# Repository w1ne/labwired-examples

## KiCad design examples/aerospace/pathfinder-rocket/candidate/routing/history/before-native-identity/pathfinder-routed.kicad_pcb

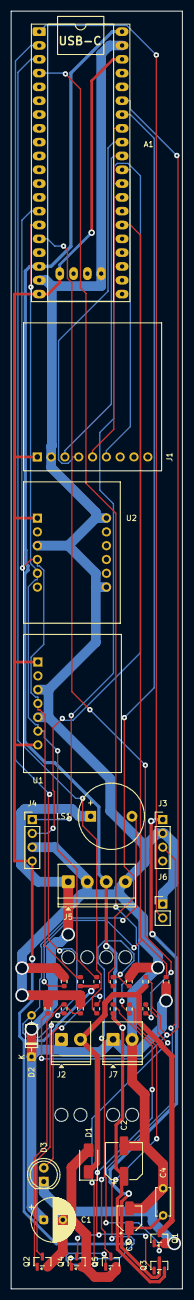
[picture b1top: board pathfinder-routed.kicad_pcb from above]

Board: 2 copper layers, 31.5 x 235.0 mm, 37 parts (0 on the bottom side), 30 nets.

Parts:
A1: MiniSTM32F411; WeAct-BlackPill-v31-body-envelope
C1: 470uF; CP_Radial_D8.0mm_P3.50mm
C2: 22uF; CP_Elec_6.3x5.4
C3: 10uF; CP_Elec_4x5.4
C4: 100nF; C_Disc_D5.0mm_W2.5mm_P5.00mm
D1: SMAJ5.0A; D_SMA
D2: 1N4148; D_DO-35_SOD27_P7.62mm_Horizontal
D3: green; LED_D5.0mm
J1: 4682; Adafruit_MicroSD_4682_CardEnvelope
J2, J7: 1984617; TerminalBlock_Phoenix_PT-1,5-2-3.5-H_1x02_P3.50mm_Horizontal
J3, J4: pin-header; PinHeader_1x04_P2.54mm_Vertical
J5: 1984633; TerminalBlock_Phoenix_PT-1,5-4-3.5-H_1x04_P3.50mm_Horizontal
J6: pin-header; PinHeader_1x02_P2.54mm_Vertical
LS1: 1536; Buzzer_12x9.5RM7.6
Q1: AO3400A; SOT-23
Q2: 2N7000; SOT-23
Q3: AO3401A; SOT-23
Q4, Q5: 2N3904; SOT-23
R1, R2, R8: 100000; R_0603_1608Metric
R3, R4: 4700; R_0603_1608Metric
R5, R9: 100; R_0603_1608Metric
R6, R10, R12: 10000; R_0603_1608Metric
R7: 47000; R_0603_1608Metric
R11: 330; R_0603_1608Metric
R13, R14: 1000; R_0603_1608Metric
U1: 2652; Adafruit_BME280_QT
U2: 3886; Adafruit_MPU6050

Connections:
+: C1.1, D2.1, J2.1, J5.1, J7.1, LS1.1, R1.1
+3V3: A1.20, A1.38, A1.41, C3.1, C4.1, J1.1, J4.4, R3.1, R4.1, U1.1, U1.7, U2.1
+5V: A1.18, A1.40, C2.1, J5.3, Q3.2, R12.1
GND: A1.19, A1.39, A1.44, C1.2, C2.2, C3.2, C4.2, D1.2, D3.1, J1.2, J3.2, J4.3, J5.2, J5.4, J6.1, J7.2, Q1.2, Q2.2, Q4.2, Q5.2, R2.2, R6.2, R8.2, R10.2, U1.3, U1.5, U2.3, U2.7, U2.12
unnamed: D2.2, LS1.2, Q2.3
unnamed: J3.1, Q3.3
unnamed: J3.3, Q5.3
unnamed: D1.1, J2.2, Q1.3, R7.1
unnamed: D3.2, R11.2
unnamed: Q2.1, R9.2, R10.1
unnamed: Q4.1, R13.2
unnamed: Q3.1, Q4.3, R12.2
unnamed: Q1.1, R5.2, R6.1
unnamed: Q5.1, R14.2
PA0: A1.26, R1.2, R2.1
PA2: A1.28, J4.1
PA3: A1.29, J4.2
PA4: A1.30, J1.6
PA5: A1.31, J1.3
PA6: A1.32, J1.4
PA7: A1.33, J1.5
PB0: A1.34, R5.1
PB1: A1.35, R7.2, R8.1
PB6: A1.14, R3.2, U1.4, U2.4
PB7: A1.15, R4.2, U1.6, U2.5
PB8: A1.16, R14.1
PB12: A1.1, J6.2
PB13: A1.2, R9.1
PB14: A1.3, R11.1
PB15: A1.4, R13.1

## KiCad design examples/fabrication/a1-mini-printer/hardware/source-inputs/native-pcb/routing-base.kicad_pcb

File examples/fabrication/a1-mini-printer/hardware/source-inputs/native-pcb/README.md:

# Routing input

`routing-base.kicad_pcb` is the fixed native output from the KiCad 10 / Freerouting 2.5.0 routing exchange. It is an intermediate input, not the accepted board. The final source applies explicit copper, topology, polarity and package corrections, then passes independent KiCad DRC.

The exact accepted starting board and original project rules are preserved under the verification evidence as `accepted-baseline/`. The original three missing nets were END_X, END_Y and Z_DIR. The routing input has all three closed; the deterministic patch sequence finishes the remaining escapes and applies the authorized electrical corrections.

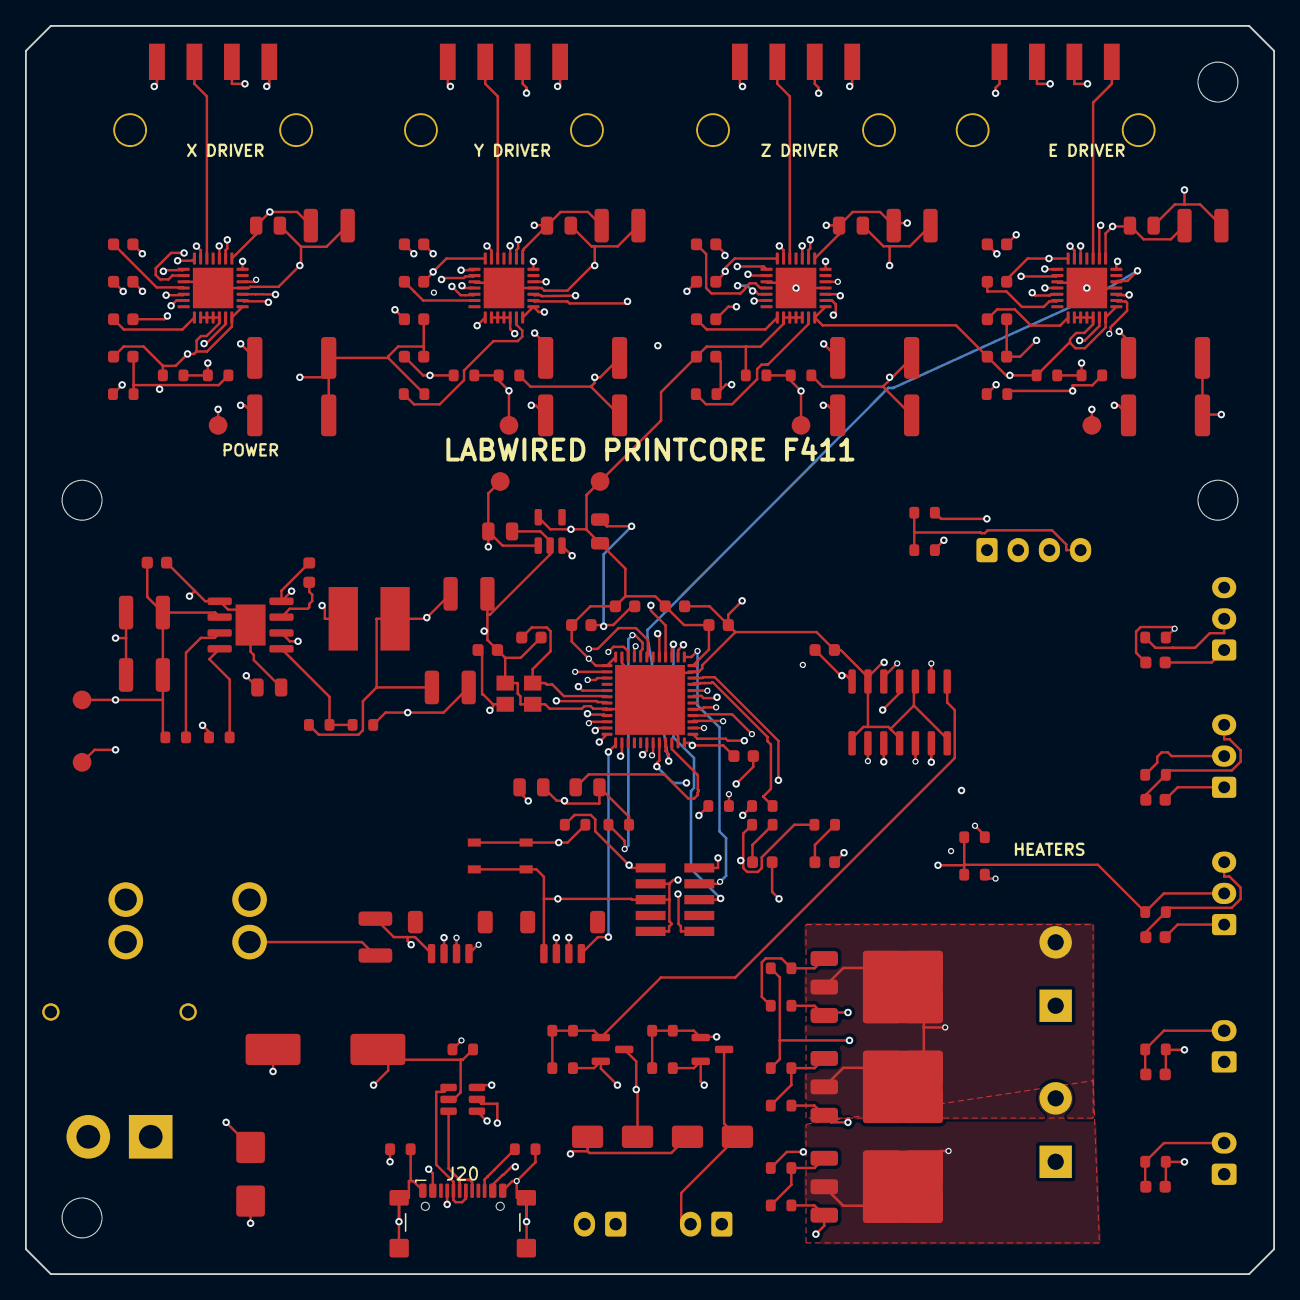
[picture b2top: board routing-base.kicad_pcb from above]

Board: 4 copper layers, 100.0 x 100.0 mm, 156 parts (0 on the bottom side), 115 nets.

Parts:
C1, C2: 12p; C_0603_1608Metric
C3: 2.2u; C_0805_2012Metric
C4, C5, C6, C7, C9, C30, C31, C33, C40, C41, C43, C50, C51, C53, C60, C61, C63, C106, C120: 100n; C_0603_1608Metric
C8, C107: 1u; C_0805_2012Metric
C32, C42, C52, C62: 220n; C_0603_1608Metric
C34, C44, C54, C64: 100n/50V; C_0805_2012Metric
C35, C45, C55, C65: 47u/50V; C_1210_3225Metric
C100: 470u/35V; CP_Elec_10x10.5
C101: 1u/50V; C_1210_3225Metric
C102, C103: 4.7u/50V; C_1210_3225Metric
C104, C105: 22u/10V; C_1210_3225Metric
C109, C110: 4.7u; C_0805_2012Metric
C112: 220n/50V; C_0603_1608Metric
C140, C141, C142, C143, C144: 10n; C_0603_1608Metric
D1: SMBJ33A; D_SMB
D3, D4: SS34; D_SMA
D10: PWR; LED_0603_1608Metric
D11: FAULT; LED_0603_1608Metric
F1: 25A MINI; Fuseholder_Blade_Mini_Keystone_3568
H1, H2, H3, H4: M3; MountingHole_3.2mm_M3
J1: 24V INPUT; AMASS_XT30PW-M_1x02_P2.50mm_Horizontal
J2: BED 24V/12A; TerminalBlock_Phoenix_MKDS-3-2-5.08_1x02_P5.08mm_Horizontal
J3: HOTEND 24V/3A; TerminalBlock_Phoenix_MKDS-3-2-5.08_1x02_P5.08mm_Horizontal
J4: FAN1; JST_XH_B2B-XH-A_1x02_P2.50mm_Vertical
J5: FAN2; JST_XH_B2B-XH-A_1x02_P2.50mm_Vertical
J10: X_MOTOR; Molex_Micro-Fit_3.0_43650-0410_1x04-1MP_P3.00mm_Horizontal
J11: Y_MOTOR; Molex_Micro-Fit_3.0_43650-0410_1x04-1MP_P3.00mm_Horizontal
J12: Z_MOTOR; Molex_Micro-Fit_3.0_43650-0410_1x04-1MP_P3.00mm_Horizontal
J13: E_MOTOR; Molex_Micro-Fit_3.0_43650-0410_1x04-1MP_P3.00mm_Horizontal
J20: USB4216-03-A_DrawingDerived_REVIEW; USB_C_Receptacle_GCT_USB4110
J21: SWD; PinHeader_2x05_P1.27mm_Vertical_SMD
J22: OLED I2C; JST_SH_BM04B-SRSS-TB_1x04-1MP_P1.00mm_Vertical
J23: UART; JST_SH_BM04B-SRSS-TB_1x04-1MP_P1.00mm_Vertical
J30: X END; JST_XH_B3B-XH-A_1x03_P2.50mm_Vertical
J31: Y END; JST_XH_B3B-XH-A_1x03_P2.50mm_Vertical
J32: Z END; JST_XH_B3B-XH-A_1x03_P2.50mm_Vertical
J33: BED NTC; JST_XH_B2B-XH-A_1x02_P2.50mm_Vertical
J34: HOT NTC; JST_XH_B2B-XH-A_1x02_P2.50mm_Vertical
J35: ESTOP/START; JST_XH_B4B-XH-A_1x04_P2.50mm_Vertical
L1: 10uH/3.2A; L_Bourns_SRN6045TA
Q1, Q2, Q3: AOD4184A; TO-252-3_TabPin2
Q4, Q5: AO3400A; SOT-23
R1, R33, R43, R53, R63, R105, R140, R141, R142, R152, R153: 10k; R_0603_1608Metric
R2, R100, R103, R121, R123, R125, R128, R129: 100k; R_0603_1608Metric
R3, R4: 22R; R_0603_1608Metric
R5, R6: 5.1k; R_0603_1608Metric
R7: 1M; R_0603_1608Metric
R30, R31, R40, R41, R50, R51, R60, R61: 0.10R; R_2512_6332Metric
R32, R42, R52, R62: 30.1k; R_0603_1608Metric
R34, R44, R54, R64, R104: 24.9k; R_0603_1608Metric
R120, R122, R124: 33R; R_0603_1608Metric
R126, R127: 100R; R_0603_1608Metric
R143, R144: 100k 0.1%; R_0603_1608Metric
R150, R151: 4.7k; R_0603_1608Metric
R160, R161: 1k; R_0603_1608Metric
SW1: RESET; SW_SPST_PTS810
TP1: X_VREF; TestPoint_Pad_D1.5mm
TP2: Y_VREF; TestPoint_Pad_D1.5mm
TP3: Z_VREF; TestPoint_Pad_D1.5mm
TP4: E_VREF; TestPoint_Pad_D1.5mm
TP20: 24V; TestPoint_Pad_D1.5mm
TP21: 5V; TestPoint_Pad_D1.5mm
TP22: 3V3; TestPoint_Pad_D1.5mm
TP23: GND; TestPoint_Pad_D1.5mm
U1: STM32F411CEU6; QFN-48-1EP_7x7mm_P0.5mm_EP5.6x5.6mm
U10, U11, U12, U13: A4988SETTR-T; TQFN-28-1EP_5x5mm_P0.5mm_EP3.25x3.25mm
U20: LMR36520A; SOIC-8-1EP_3.9x4.9mm_P1.27mm_EP2.41x3.3mm
U21: AP2112K-3.3; SOT-23-5
U30: 74HCT125D; SOIC-14_3.9x8.7mm_P1.27mm
U31: USBLC6-2SC6; SOT-23-6
Y1: 8MHz; Crystal_SMD_3225-4Pin_3.2x2.5mm

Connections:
+3V3: C4.1, C5.1, C6.1, C7.1, C9.1, C33.1, C43.1, C53.1, C63.1, C110.1, J21.1, J22.2, J23.2, J30.2, J31.2, J32.2, J35.4, R1.1, R32.1, R42.1, R52.1, R62.1, R105.1, R140.1, R141.1, R142.1, R150.1, R151.1, R152.1, R153.1, R160.1, R161.1, TP22.1, U1.1, U1.24, U1.36, U1.48, U10.9, U10.10, U10.11, U10.12, U10.14, U10.15, U11.9, U11.10, U11.11, U11.12, U11.14, U11.15, U12.9, U12.10, U12.11, U12.12, U12.14, U12.15, U13.9, U13.10, U13.11, U13.12, U13.14, U13.15, U21.5
+3V3A: C8.1, J33.1, J34.1, U1.9
+5V: C104.1, C105.1, C109.1, C120.1, L1.2, R103.1, TP21.1, U21.1, U21.3, U30.14
+24V: C31.2, C34.1, C35.1, C41.2, C44.1, C45.1, C51.2, C54.1, C55.1, C61.2, C64.1, C65.1, C100.1, C101.1, C102.1, C103.1, C112.1, D1.1, D3.1, D4.1, F1.2, J2.1, J3.1, J4.1, J5.1, R100.1, TP20.1, U10.22, U10.28, U11.22, U11.28, U12.22, U12.28, U13.22, U13.28, U20.2
+24VIN: F1.1, J1.1
BED_CMD: U1.27, U30.5
BED_GATE: R120.1, R122.1, U30.6
BED_GATE_A: Q1.1, R120.2, R121.1
BED_GATE_B: Q2.1, R122.2, R123.1
BED_SW: J2.2, Q1.2, Q2.2
BOOT0: R2.1, U1.44
BUCK_BOOT: C106.1, U20.7
BUCK_EN: R100.2, U20.3
BUCK_FB: R103.2, R104.1, U20.5
BUCK_PG: R105.2, U20.4
BUCK_SW: C106.2, L1.1, U20.8
BUCK_VCC: C107.1, U20.6
CC1: J20.A5, R5.1
CC2: J20.B5, R6.1
DRV_EN: U1.25, U10.2, U11.2, U12.2, U13.2
END_X: C140.1, J30.3, R140.2, U1.29
END_Y: C141.1, J31.3, R141.2, U1.2
END_Z: C142.1, J32.3, R142.2, U1.3
ESTOP: J35.2, R152.2, U1.20
E_A+: J13.1, U13.24
E_A-: J13.2, U13.21
E_B+: J13.3, U13.26
E_B-: J13.4, U13.1
E_CP1: C60.1, U13.4
E_CP2: C60.2, U13.5
E_DIR: U1.21, U13.19
E_ROSC: R64.1, U13.13
E_S1: R60.1, U13.23
E_S2: R61.1, U13.27
E_STEP: U1.46, U13.16
E_VCP: C61.1, U13.6
E_VREF: R62.2, R63.1, TP4.1, U13.17
E_VREG: C62.1, U13.8
FAN1_CMD: U1.28, U30.9
FAN1_GATE: Q4.1, R126.1, R126.2, R128.1, U30.8
FAN1_SW: D3.2, J4.2, Q4.3
FAN2_CMD: U1.10, U30.12
FAN2_GATE: Q5.1, R127.1, R127.2, R129.1, U30.11
FAN2_SW: D4.2, J5.2, Q5.3
GND: C1.2, C2.2, C3.2, C4.2, C5.2, C6.2, C7.2, C8.2, C9.2, C32.2, C33.2, C34.2, C35.2, C42.2, C43.2, C44.2, C45.2, C52.2, C53.2, C54.2, C55.2, C62.2, C63.2, C64.2, C65.2, C100.2, C101.2, C102.2, C103.2, C104.2, C105.2, C107.2, C109.2, C110.2, C112.2, C120.2, C140.2, C141.2, C142.2, C143.2, C144.2, D1.2, D10.2, J1.2, J20.A1, J20.A12, J20.B1, J20.B12, J20.SH, J21.3, J21.5, J21.9, J22.1, J23.1, J30.1, J31.1, J32.1, J35.1, Q1.3, Q2.3, Q3.3, Q4.2, Q5.2, R2.2, R5.2, R6.2, R7.2, R30.2, R31.2, R33.2, R34.2, R40.2, R41.2, R43.2, R44.2, R50.2, R51.2, R53.2, R54.2, R60.2, R61.2, R63.2, R64.2, R104.2, R121.2, R123.2, R125.2, R128.2, R129.2, R143.2, R144.2, SW1.2, TP23.1, U1.8, U1.23, U1.35, U1.47, U1.49, U10.3, U10.18, U10.29, U11.3, U11.18, U11.29, U12.3, U12.18, U12.29, U13.3, U13.18, U13.29, U20.1, U20.9, U21.2, U30.1, U30.4, U30.7, U30.10, U30.13, U31.2, Y1.2, Y1.4
HOTEND_CMD: U1.26, U30.2
HOT_GATE: R124.1, U30.3
HOT_GATE_Q: Q3.1, R124.2, R125.1
HOT_SW: J3.2, Q3.2
I2C_SCL: J22.3, R150.2, U1.42
I2C_SDA: J22.4, R151.2, U1.43
LED_FAULT_A: D11.1, R161.2
LED_PWR_A: D10.1, R160.2
NRST: J21.10, R1.2, SW1.1, U1.7
OSC_IN: C1.1, U1.5, Y1.1
OSC_OUT: C2.1, U1.6, Y1.3
START: J35.3, R153.2, U1.38
SWCLK: J21.4, U1.37
SWDIO: J21.2, U1.34
TH_BED: C143.1, J33.2, R143.1, U1.11
TH_HOT: C144.1, J34.2, R144.1, U1.14
UART_RX: J23.4, U1.13
UART_TX: J23.3, U1.12
USB_DM: R3.2, U1.32
USB_DM_CONN: J20.A7, J20.B7, U31.1
USB_DM_MCU: R3.1, U31.6
USB_DP: R4.2, U1.33
USB_DP_CONN: J20.A6, J20.B6, U31.3
USB_DP_MCU: R4.1, U31.4
USB_VBUS: J20.A4, J20.A9, J20.B4, J20.B9, U31.5
USB_VBUS_SENSE: R7.1, U1.30
USER_AUX: D11.2, U1.31
VCAP1: C3.1, U1.22
X_A+: J10.1, U10.24
X_A-: J10.2, U10.21
X_B+: J10.3, U10.26
X_B-: J10.4, U10.1
X_CP1: C30.1, U10.4
X_CP2: C30.2, U10.5
X_DIR: U1.19, U10.19
X_ROSC: R34.1, U10.13
X_S1: R30.1, U10.23
X_S2: R31.1, U10.27
X_STEP: U1.18, U10.16
X_VCP: C31.1, U10.6
X_VREF: R32.2, R33.1, TP1.1, U10.17
X_VREG: C32.1, U10.8
Y_A+: J11.1, U11.24
Y_A-: J11.2, U11.21
Y_B+: J11.3, U11.26
Y_B-: J11.4, U11.1
Y_CP1: C40.1, U11.4
Y_CP2: C40.2, U11.5
Y_DIR: U1.40, U11.19
Y_ROSC: R44.1, U11.13
Y_S1: R40.1, U11.23
Y_S2: R41.1, U11.27
Y_STEP: J21.6, U1.39, U11.16
Y_VCP: C41.1, U11.6
Y_VREF: R42.2, R43.1, TP2.1, U11.17
Y_VREG: C42.1, U11.8
Z_A+: J12.1, U12.24
Z_A-: J12.2, U12.21
Z_B+: J12.3, U12.26
Z_B-: J12.4, U12.1
Z_CP1: C50.1, U12.4
Z_CP2: C50.2, U12.5
Z_DIR: U1.45, U12.19
Z_ROSC: R54.1, U12.13
Z_S1: R50.1, U12.23
Z_S2: R51.1, U12.27
Z_STEP: U1.41, U12.16
Z_VCP: C51.1, U12.6
Z_VREF: R52.2, R53.1, TP3.1, U12.17
Z_VREG: C52.1, U12.8

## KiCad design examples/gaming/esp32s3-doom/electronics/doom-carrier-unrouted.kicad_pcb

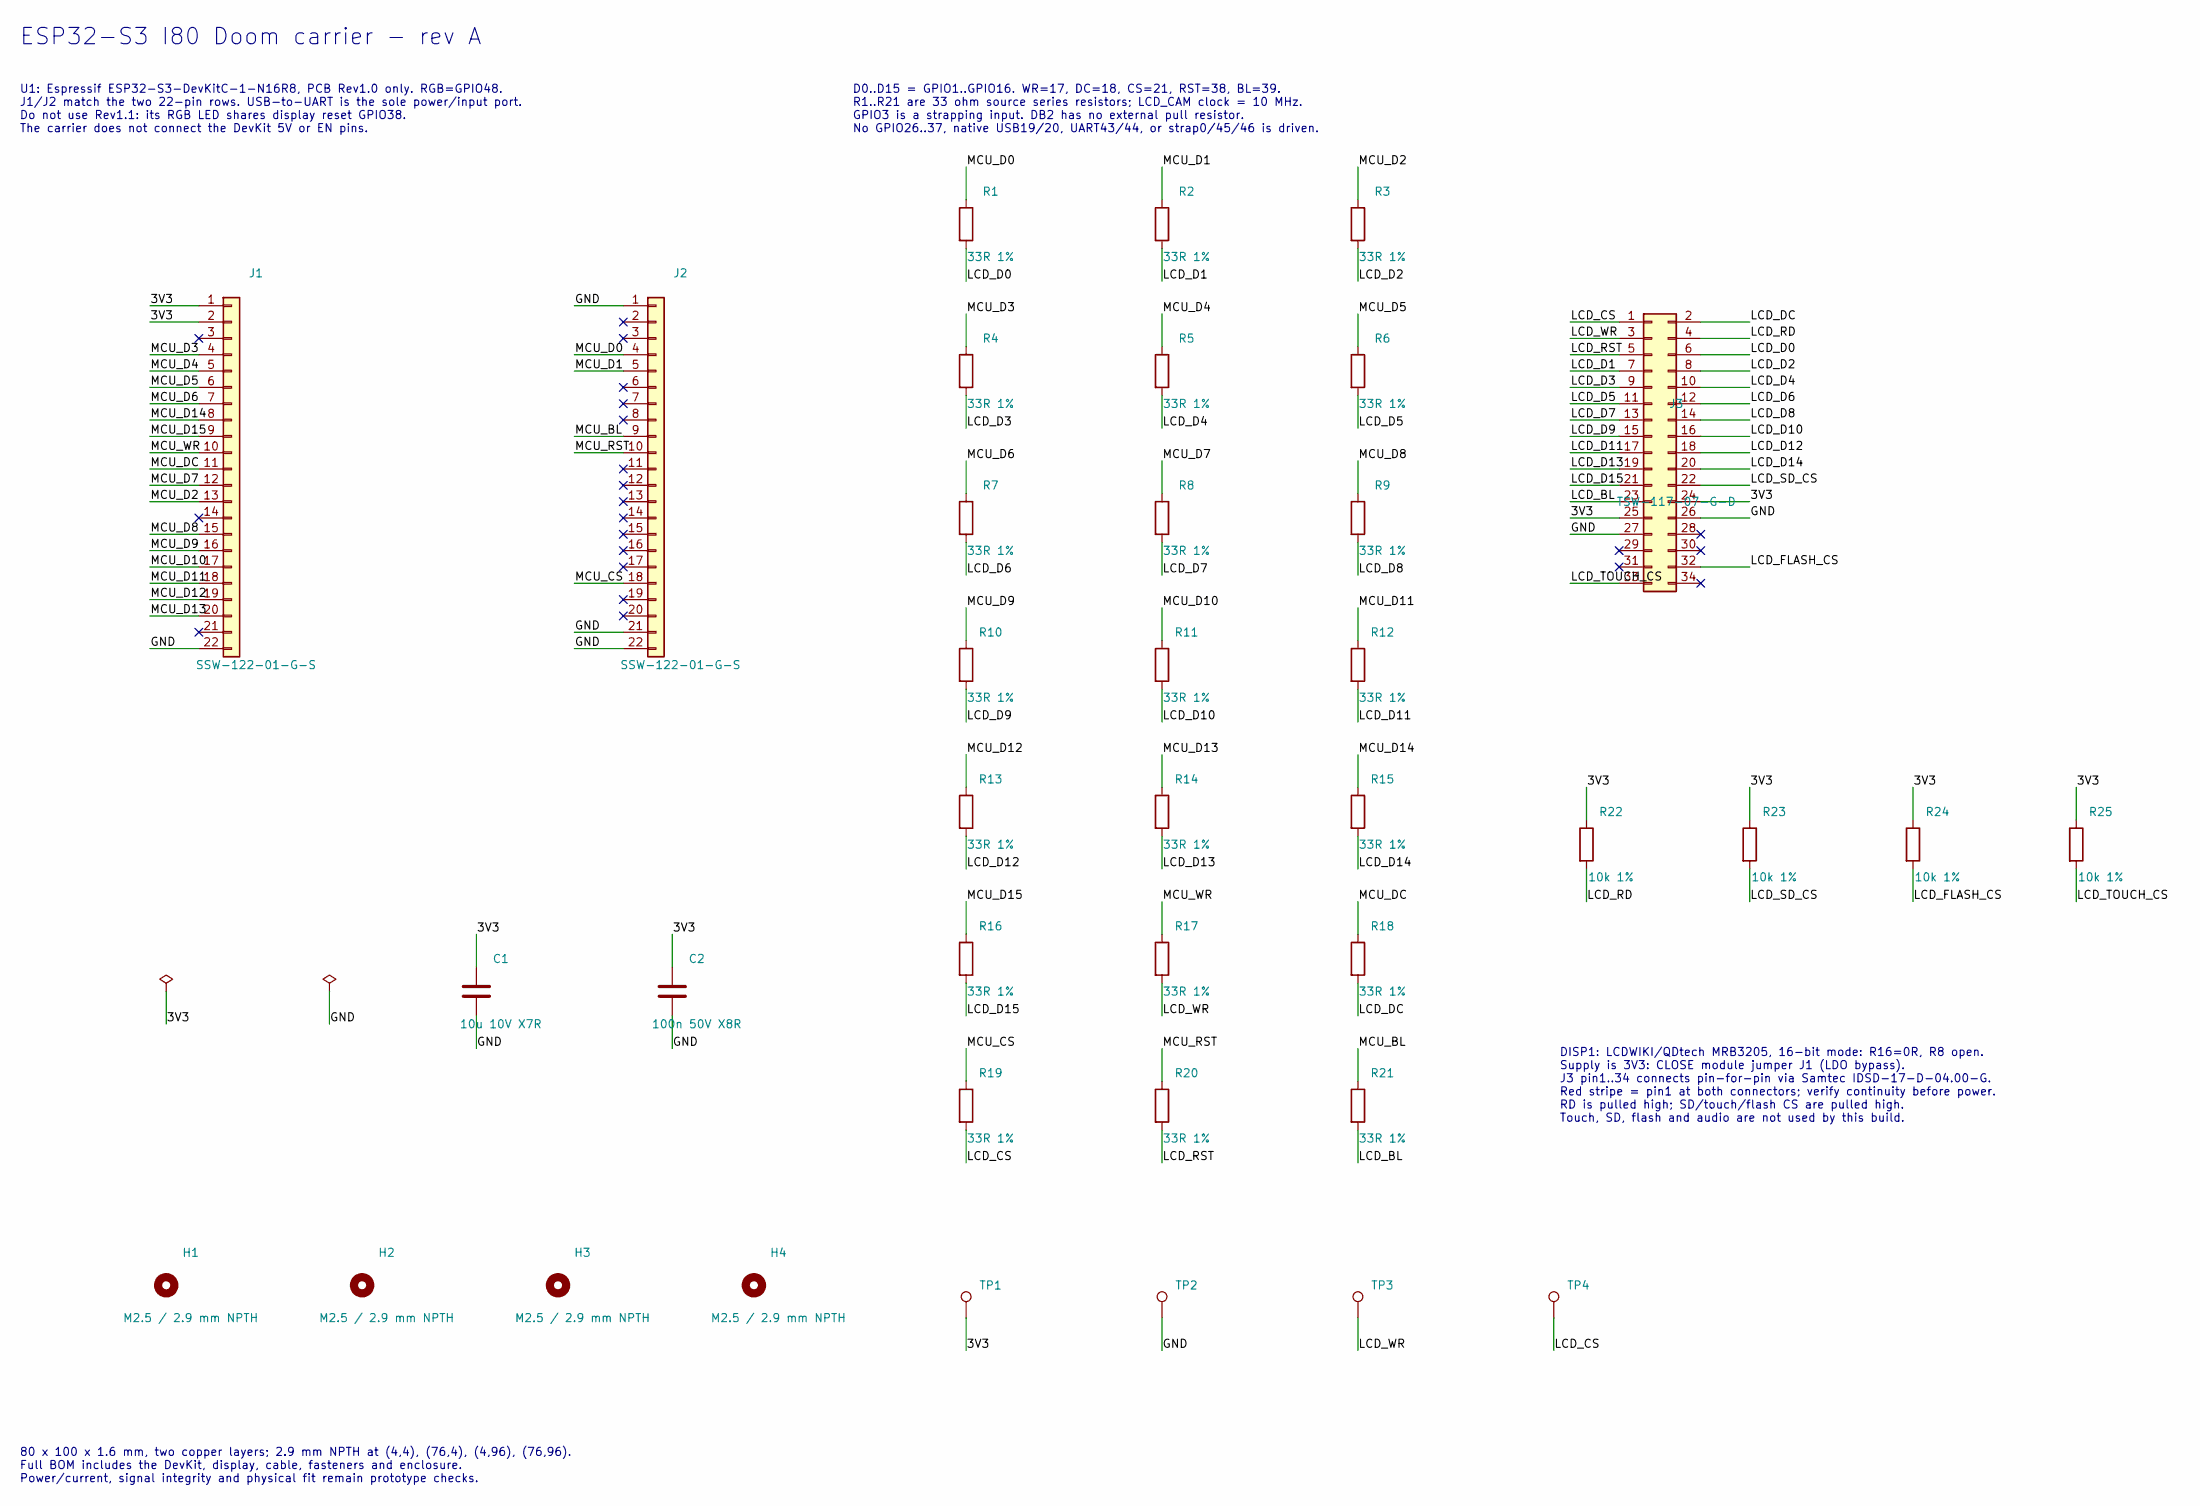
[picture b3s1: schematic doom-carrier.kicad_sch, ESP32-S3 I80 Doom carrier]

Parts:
C1: 10u 10V X7R; C; MPN C2012X7R1A106K125AC
C2: 100n 50V X8R; C; MPN C2012X8R1H104K125AA
H1, H2, H3, H4: M2.5 / 2.9 mm NPTH; MountingHole
J1, J2: SSW-122-01-G-S; Socket22; MPN SSW-122-01-G-S
J3: TSW-117-07-G-D; Display34; MPN TSW-117-07-G-D
R1, R2, R3, R4, R5, R6, R7, R8, R9, R10, R11, R12, R13, R14, R15, R16, R17, R18, R19, R20, R21: 33R 1%; R; MPN RC0603FR-0733RL
R22, R23, R24, R25: 10k 1%; R; MPN RC0603FR-0710KL
TP1: 3V3; TestPoint
TP2: GND; TestPoint
TP3: LCD_WR; TestPoint
TP4: LCD_CS; TestPoint

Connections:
/3V3: C1.1, C2.1, J1.1, J1.2, J3.24, J3.25, R22.1, R23.1, R24.1, R25.1, TP1.1
/GND: C1.2, C2.2, J1.22, J2.1, J2.21, J2.22, J3.26, J3.27, TP2.1
/LCD_BL: J3.23, R21.2
/LCD_CS: J3.1, R19.2, TP4.1
/LCD_D0: J3.6, R1.2
/LCD_D1: J3.7, R2.2
/LCD_D2: J3.8, R3.2
/LCD_D3: J3.9, R4.2
/LCD_D4: J3.10, R5.2
/LCD_D5: J3.11, R6.2
/LCD_D6: J3.12, R7.2
/LCD_D7: J3.13, R8.2
/LCD_D8: J3.14, R9.2
/LCD_D9: J3.15, R10.2
/LCD_D10: J3.16, R11.2
/LCD_D11: J3.17, R12.2
/LCD_D12: J3.18, R13.2
/LCD_D13: J3.19, R14.2
/LCD_D14: J3.20, R15.2
/LCD_D15: J3.21, R16.2
/LCD_DC: J3.2, R18.2
/LCD_FLASH_CS: J3.32, R24.2
/LCD_RD: J3.4, R22.2
/LCD_RST: J3.5, R20.2
/LCD_SD_CS: J3.22, R23.2
/LCD_TOUCH_CS: J3.33, R25.2
/LCD_WR: J3.3, R17.2, TP3.1
/MCU_BL: J2.9, R21.1
/MCU_CS: J2.18, R19.1
/MCU_D0: J2.4, R1.1
/MCU_D1: J2.5, R2.1
/MCU_D2: J1.13, R3.1
/MCU_D3: J1.4, R4.1
/MCU_D4: J1.5, R5.1
/MCU_D5: J1.6, R6.1
/MCU_D6: J1.7, R7.1
/MCU_D7: J1.12, R8.1
/MCU_D8: J1.15, R9.1
/MCU_D9: J1.16, R10.1
/MCU_D10: J1.17, R11.1
/MCU_D11: J1.18, R12.1
/MCU_D12: J1.19, R13.1
/MCU_D13: J1.20, R14.1
/MCU_D14: J1.8, R15.1
/MCU_D15: J1.9, R16.1
/MCU_DC: J1.11, R18.1
/MCU_RST: J2.10, R20.1
/MCU_WR: J1.10, R17.1

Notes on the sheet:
ESP32-S3 I80 Doom carrier - rev A
U1: Espressif ESP32-S3-DevKitC-1-N16R8, PCB Rev1.0 only. RGB=GPIO48. J1/J2 match the two 22-pin rows. USB-to-UART is the sole power/input port. Do not use Rev1.1: its RGB LED shares display reset GPIO38. The carrier does not connect the DevKit 5V or EN pins.
D0..D15 = GPIO1..GPIO16. WR=17, DC=18, CS=21, RST=38, BL=39. R1..R21 are 33 ohm source series resistors; LCD_CAM clock = 10 MHz. GPIO3 is a strapping input. DB2 has no external pull resistor. No GPIO26..37, native USB19/20, UART43/44, or strap0/45/46 is driven.
DISP1: LCDWIKI/QDtech MRB3205, 16-bit mode: R16=0R, R8 open. Supply is 3V3: CLOSE module jumper J1 (LDO bypass). J3 pin1..34 connects pin-for-pin via Samtec IDSD-17-D-04.00-G. Red stripe = pin1 at both connectors; verify continuity before power. RD is pulled high; SD/touch/flash CS are pulled high.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
80 x 100 x 1.6 mm, two copper layers; 2.9 mm NPTH at (4,4), (76,4), (4,96), (76,96). Full BOM includes the DevKit, display, cable, fasteners and enclosure. Power/current, signal integrity and physical fit remain prototype checks.

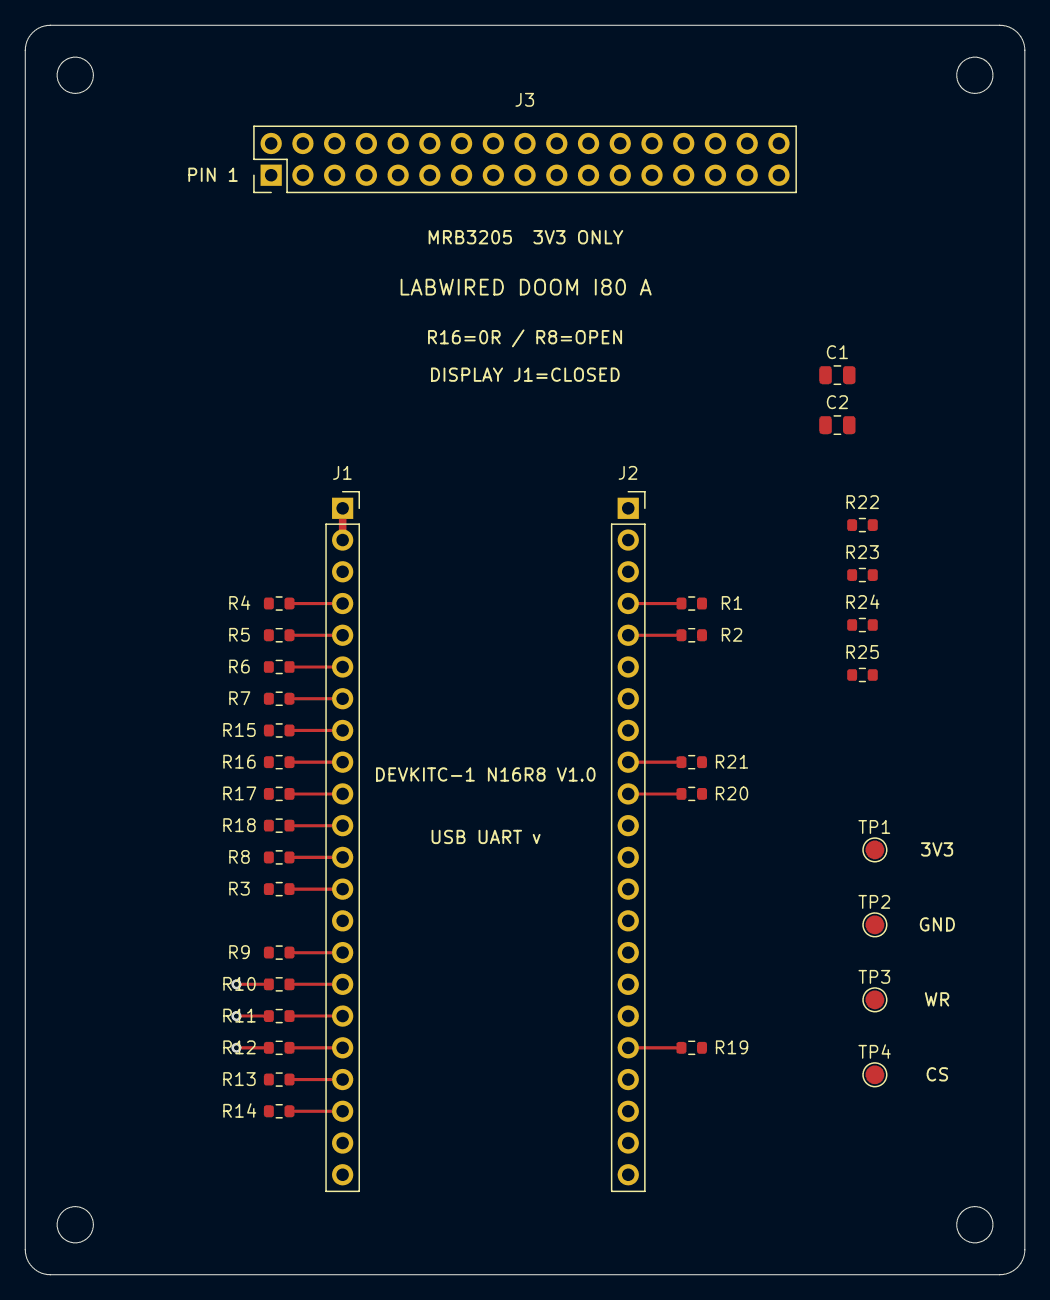
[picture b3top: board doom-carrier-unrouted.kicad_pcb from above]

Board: 2 copper layers, 80.0 x 100.0 mm, 38 parts (0 on the bottom side), 48 nets.

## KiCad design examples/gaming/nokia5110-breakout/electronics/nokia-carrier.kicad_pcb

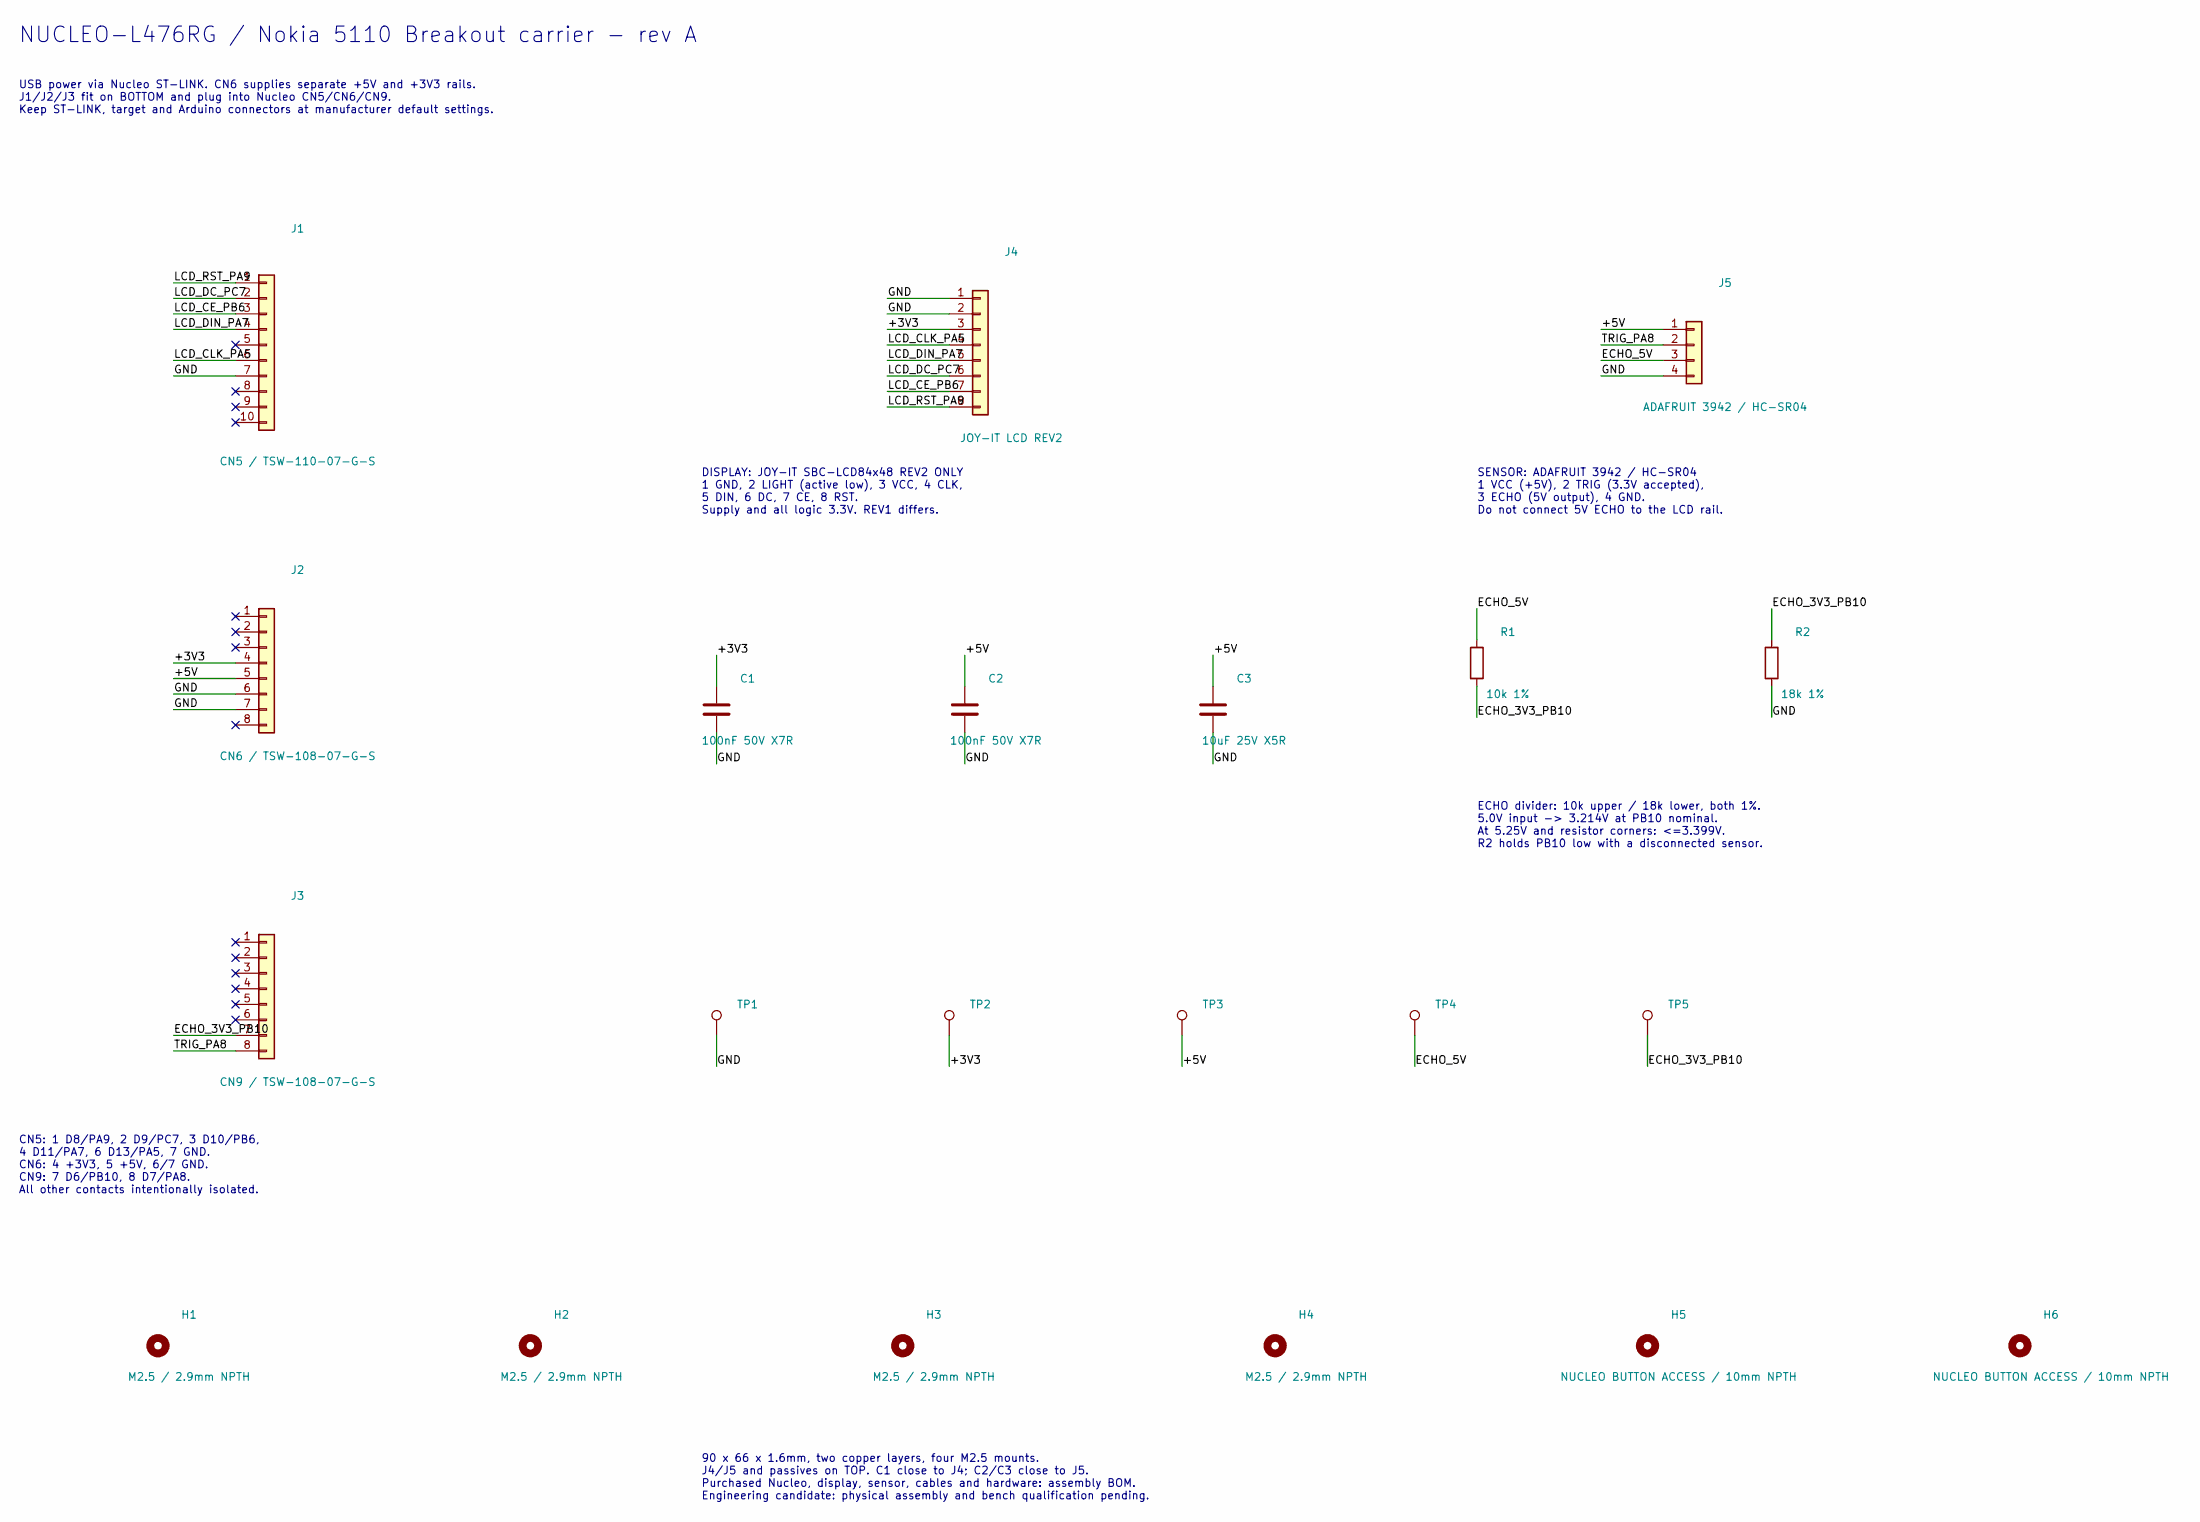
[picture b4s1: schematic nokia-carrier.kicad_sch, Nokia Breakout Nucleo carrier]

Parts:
C1, C2: 100nF 50V X7R; C; MPN C1608X7R1H104K080AA
C3: 10uF 25V X5R; C0805; MPN C2012X5R1E106K125AB
H1, H2, H3, H4: M2.5 / 2.9mm NPTH; MountingHole
H5, H6: NUCLEO BUTTON ACCESS / 10mm NPTH; AccessHole
J1: CN5 / TSW-110-07-G-S; Header10; MPN TSW-110-07-G-S
J2: CN6 / TSW-108-07-G-S; Header8; MPN TSW-108-07-G-S
J3: CN9 / TSW-108-07-G-S; Header8; MPN TSW-108-07-G-S
J4: JOY-IT LCD REV2; Header8; MPN TSW-108-07-G-S
J5: ADAFRUIT 3942 / HC-SR04; Header4; MPN TSW-104-07-G-S
R1: 10k 1%; R; MPN RC0603FR-0710KL
R2: 18k 1%; R; MPN RC0603FR-0718KL
TP1: GND; TestPoint
TP2: +3V3; TestPoint
TP3: +5V; TestPoint
TP4: ECHO_5V; TestPoint
TP5: ECHO_3V3_PB10; TestPoint

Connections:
/+3V3: C1.1, J2.4, J4.3, TP2.1
/+5V: C2.1, C3.1, J2.5, J5.1, TP3.1
/ECHO_3V3_PB10: J3.7, R1.2, R2.1, TP5.1
/ECHO_5V: J5.3, R1.1, TP4.1
/GND: C1.2, C2.2, C3.2, J1.7, J2.6, J2.7, J4.1, J4.2, J5.4, R2.2, TP1.1
/LCD_CE_PB6: J1.3, J4.7
/LCD_CLK_PA5: J1.6, J4.4
/LCD_DC_PC7: J1.2, J4.6
/LCD_DIN_PA7: J1.4, J4.5
/LCD_RST_PA9: J1.1, J4.8
/TRIG_PA8: J3.8, J5.2

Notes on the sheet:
NUCLEO-L476RG / Nokia 5110 Breakout carrier - rev A
USB power via Nucleo ST-LINK. CN6 supplies separate +5V and +3V3 rails. J1/J2/J3 fit on BOTTOM and plug into Nucleo CN5/CN6/CN9. Keep ST-LINK, target and Arduino connectors at manufacturer default settings.
DISPLAY: JOY-IT SBC-LCD84x48 REV2 ONLY 1 GND, 2 LIGHT (active low), 3 VCC, 4 CLK, 5 DIN, 6 DC, 7 CE, 8 RST. Supply and all logic 3.3V. REV1 differs.
SENSOR: ADAFRUIT 3942 / HC-SR04 1 VCC (+5V), 2 TRIG (3.3V accepted), 3 ECHO (5V output), 4 GND. Do not connect 5V ECHO to the LCD rail.
ECHO divider: 10k upper / 18k lower, both 1%. 5.0V input -> 3.214V at PB10 nominal. At 5.25V and resistor corners: <=3.399V. R2 holds PB10 low with a disconnected sensor.
CN5: 1 D8/PA9, 2 D9/PC7, 3 D10/PB6, 4 D11/PA7, 6 D13/PA5, 7 GND. CN6: 4 +3V3, 5 +5V, 6/7 GND. CN9: 7 D6/PB10, 8 D7/PA8. All other contacts intentionally isolated.
90 x 66 x 1.6mm, two copper layers, four M2.5 mounts. J4/J5 and passives on TOP. C1 close to J4; C2/C3 close to J5. Purchased Nucleo, display, sensor, cables and hardware: assembly BOM. Engineering candidate: physical assembly and bench qualification pending.

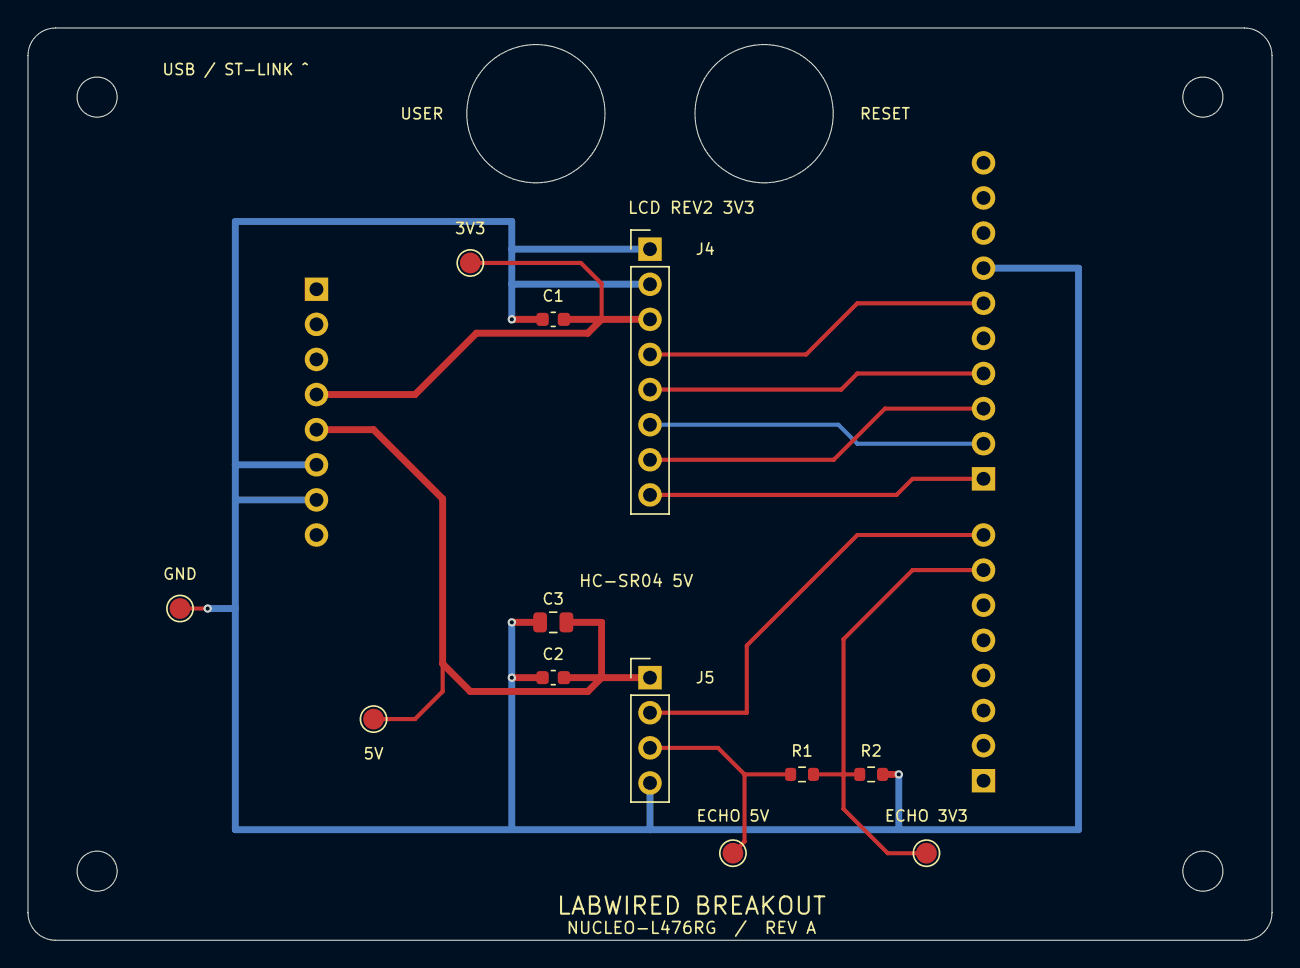
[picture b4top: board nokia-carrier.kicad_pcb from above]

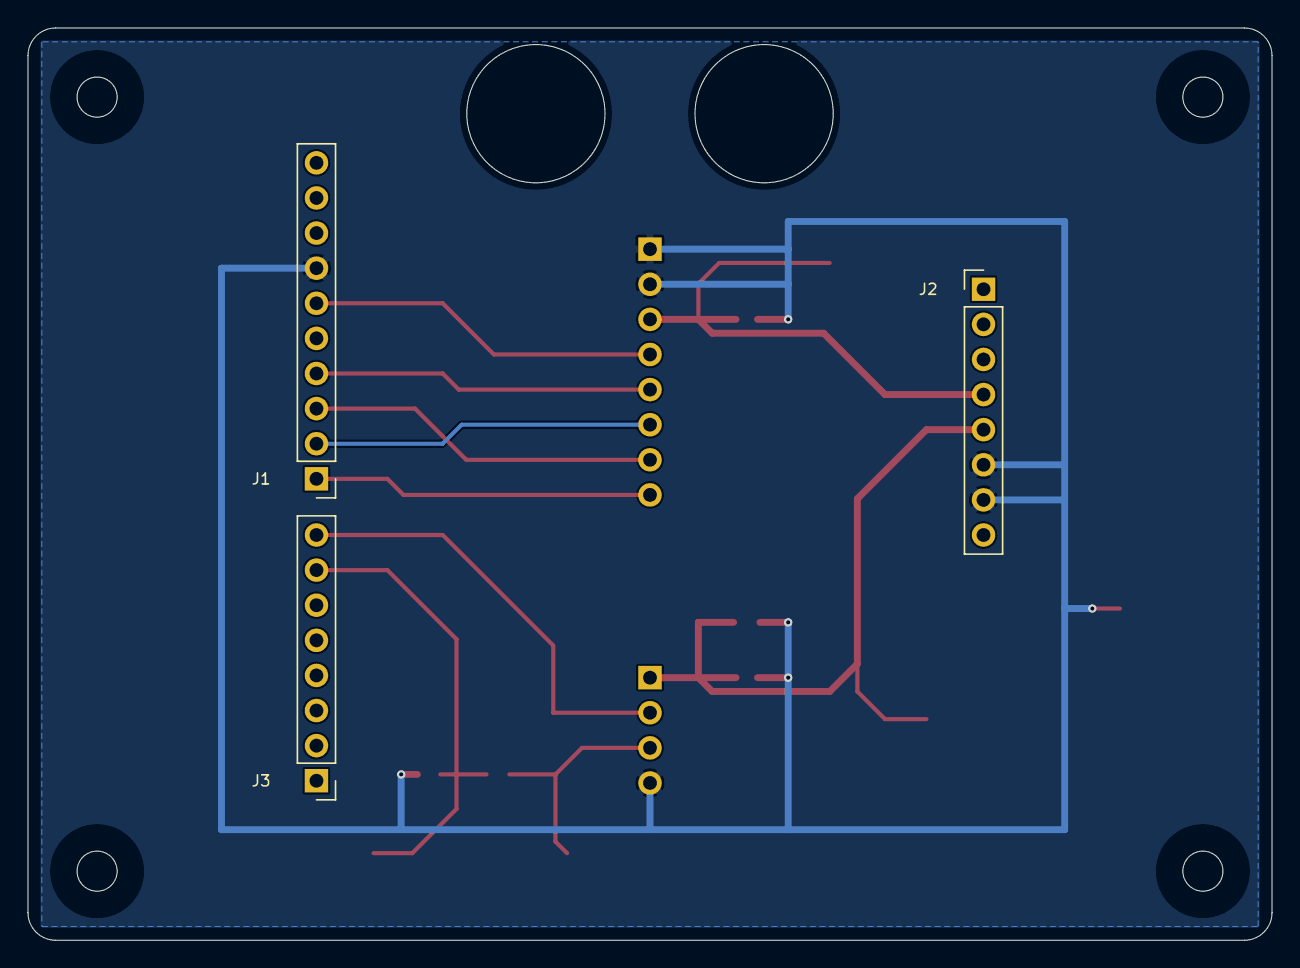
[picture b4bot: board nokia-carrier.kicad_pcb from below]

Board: 2 copper layers, 90.0 x 66.0 mm, 21 parts (3 on the bottom side), 11 nets.
